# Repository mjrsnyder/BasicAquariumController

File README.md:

# BasicAquariumController

### Goals
* Monitor and report tempurature
* Monitor and report tank water level
* Monitor and report top-off water level
* Control 12v fan for cooling
* Control 12v pump for top-off and maybe water changes
* Control lights using an IR transmitter
* Use as many on-hand components as possible
* Avoid controlling mains power
* Inexpensive
* Expandable via i2c
* Controllable with HomeAssistant but also have built failsafes in case HA is unavailable

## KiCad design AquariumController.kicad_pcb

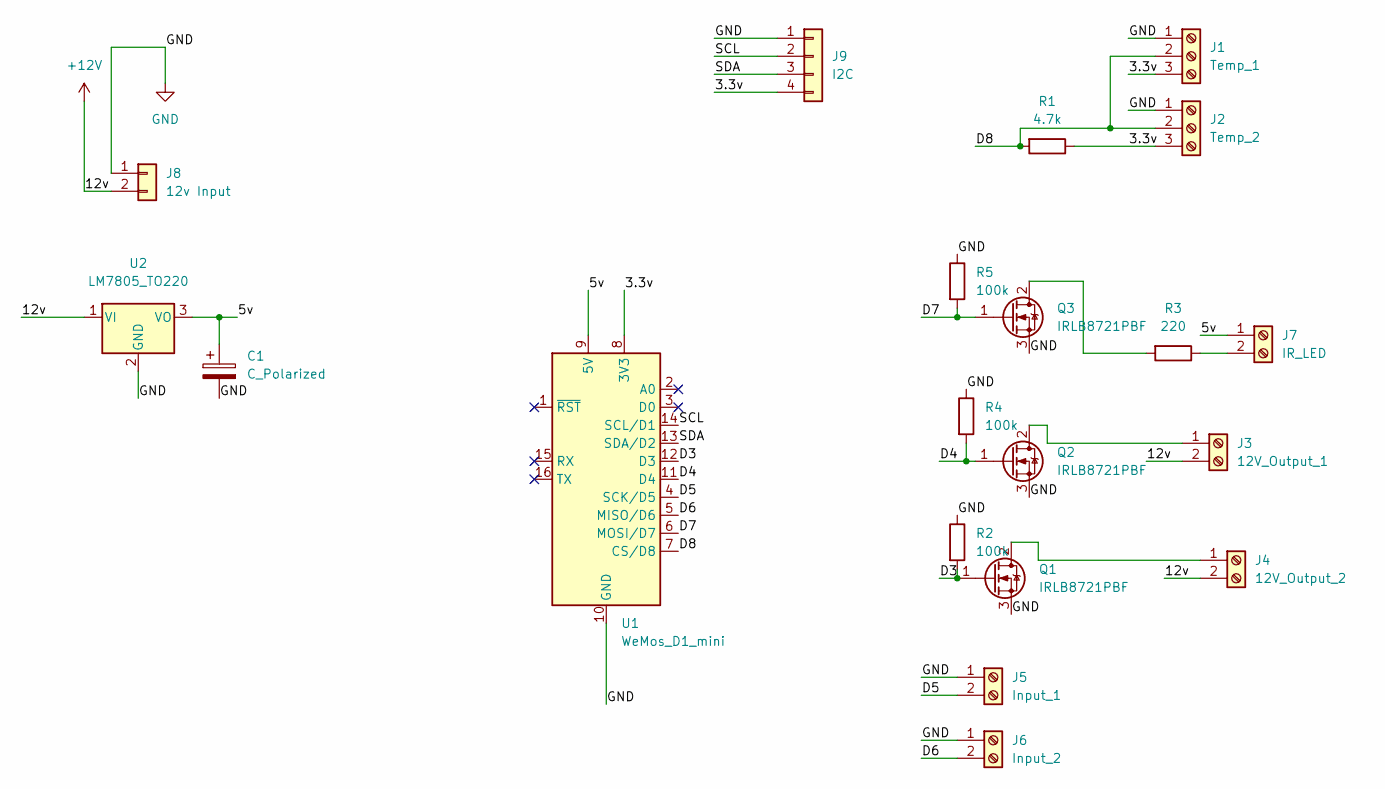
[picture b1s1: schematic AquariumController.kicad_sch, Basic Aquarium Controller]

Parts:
C1: C_Polarized; C_Radial_D5.0mm_H11.0mm_P2.00mm
J1: Temp_1; TerminalBlock_Phoenix_MKDS-1,5-3-5.08_1x03_P5.08mm_Horizont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
J2: Temp_2; TerminalBlock_Phoenix_MKDS-1,5-3-5.08_1x03_P5.08mm_Horizont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
J3: 12V_Output_1; TerminalBlock_Phoenix_MKDS-1,5-2-5.08_1x02_P5.08mm_Horizont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
J4: 12V_Output_2; TerminalBlock_Phoenix_MKDS-1,5-2-5.08_1x02_P5.08mm_Horizont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
J5: Input_1; TerminalBlock_Phoenix_MKDS-1,5-2-5.08_1x02_P5.08mm_Horizont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
J6: Input_2; TerminalBlock_Phoenix_MKDS-1,5-2-5.08_1x02_P5.08mm_Horizont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
J7: IR_LED; TerminalBlock_Phoenix_MKDS-1,5-2-5.08_1x02_P5.08mm_Horizont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
J8: 12v Input; JST_XH_B2B-XH-A_1x02_P2.50mm_Vertical
J9: I2C; JST_XH_S4B-XH-A_1x04_P2.50mm_Horizontal
Q1, Q2, Q3: IRLB8721PBF; TO-220-3_Vertical
R1: 4.7k; R_Axial_DIN0207_L6.3mm_D2.5mm_P10.16mm_Horizontal
R2, R4, R5: 100k; R_Axial_DIN0207_L6.3mm_D2.5mm_P10.16mm_Horizontal
R3: 220; R_Axial_DIN0207_L6.3mm_D2.5mm_P10.16mm_Horizontal
U1: WeMos_D1_mini; WEMOS_D1_mini_light
U2: LM7805_TO220; TO-220-3_Vertical

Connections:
+12V: J3.2, J4.2, J8.2, U2.1 (VI)
/3.3v: J1.3, J2.3, J9.4, R1.1, U1.8 (3V3)
/5v: C1.1, J7.1, U1.9 (5V), U2.3 (VO)
/D3: Q1.1 (G), R2.2, U1.12 (D3)
/D4: Q2.1 (G), R4.2, U1.11 (D4)
/D5: J5.2, U1.4 (SCK/D5)
/D6: J6.2, U1.5 (MISO/D6)
/D7: Q3.1 (G), R5.2, U1.6 (MOSI/D7)
/D8: J1.2, J2.2, R1.2, U1.7 (CS/D8)
/SCL: J9.2, U1.14 (SCL/D1)
/SDA: J9.3, U1.13 (SDA/D2)
GND: C1.2, J1.1, J2.1, J5.1, J6.1, J8.1, J9.1, Q1.3 (S), Q2.3 (S), Q3.3 (S), R2.1, R4.1, R5.1, U1.10 (GND), U2.2 (GND)
unnamed: J3.1, Q2.2 (D)
unnamed: J4.1, Q1.2 (D)
unnamed: J7.2, R3.1
unnamed: Q3.2 (D), R3.2

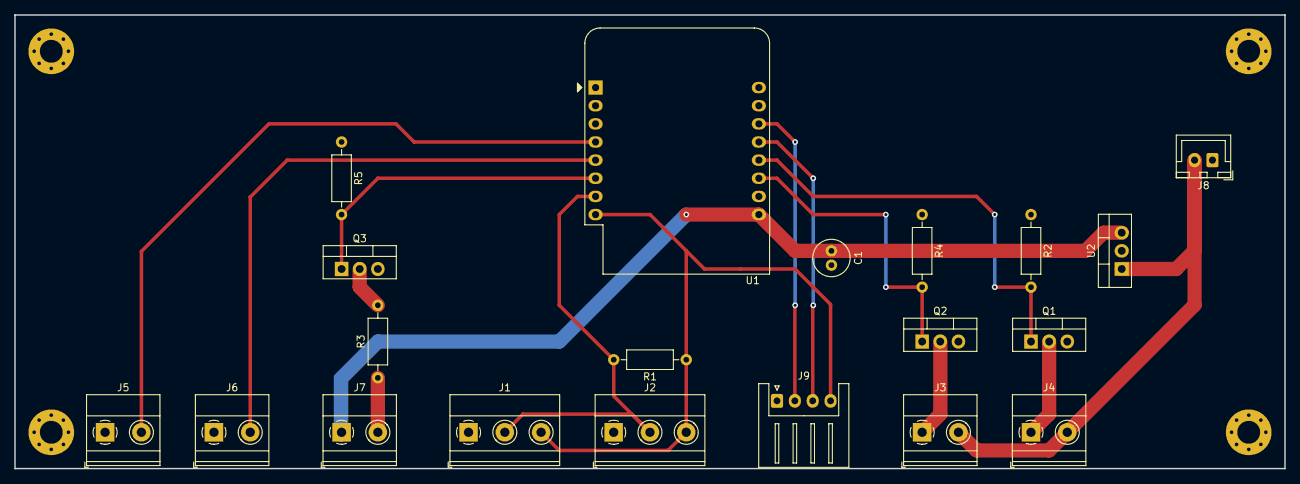
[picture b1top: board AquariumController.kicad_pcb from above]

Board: 2 copper layers, 177.8 x 63.5 mm, 20 parts (0 on the bottom side), 16 nets.

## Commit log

2022-09-14 Swap out all the mosfets/bjts add the i2c breakout flip the power to the right side
2022-09-14 tweaks
2022-09-15 make the holes not on the schematic and fix the name of the 12v input
